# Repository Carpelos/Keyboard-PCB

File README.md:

# Keyboard PCB
 Mi primera PCB de teclado

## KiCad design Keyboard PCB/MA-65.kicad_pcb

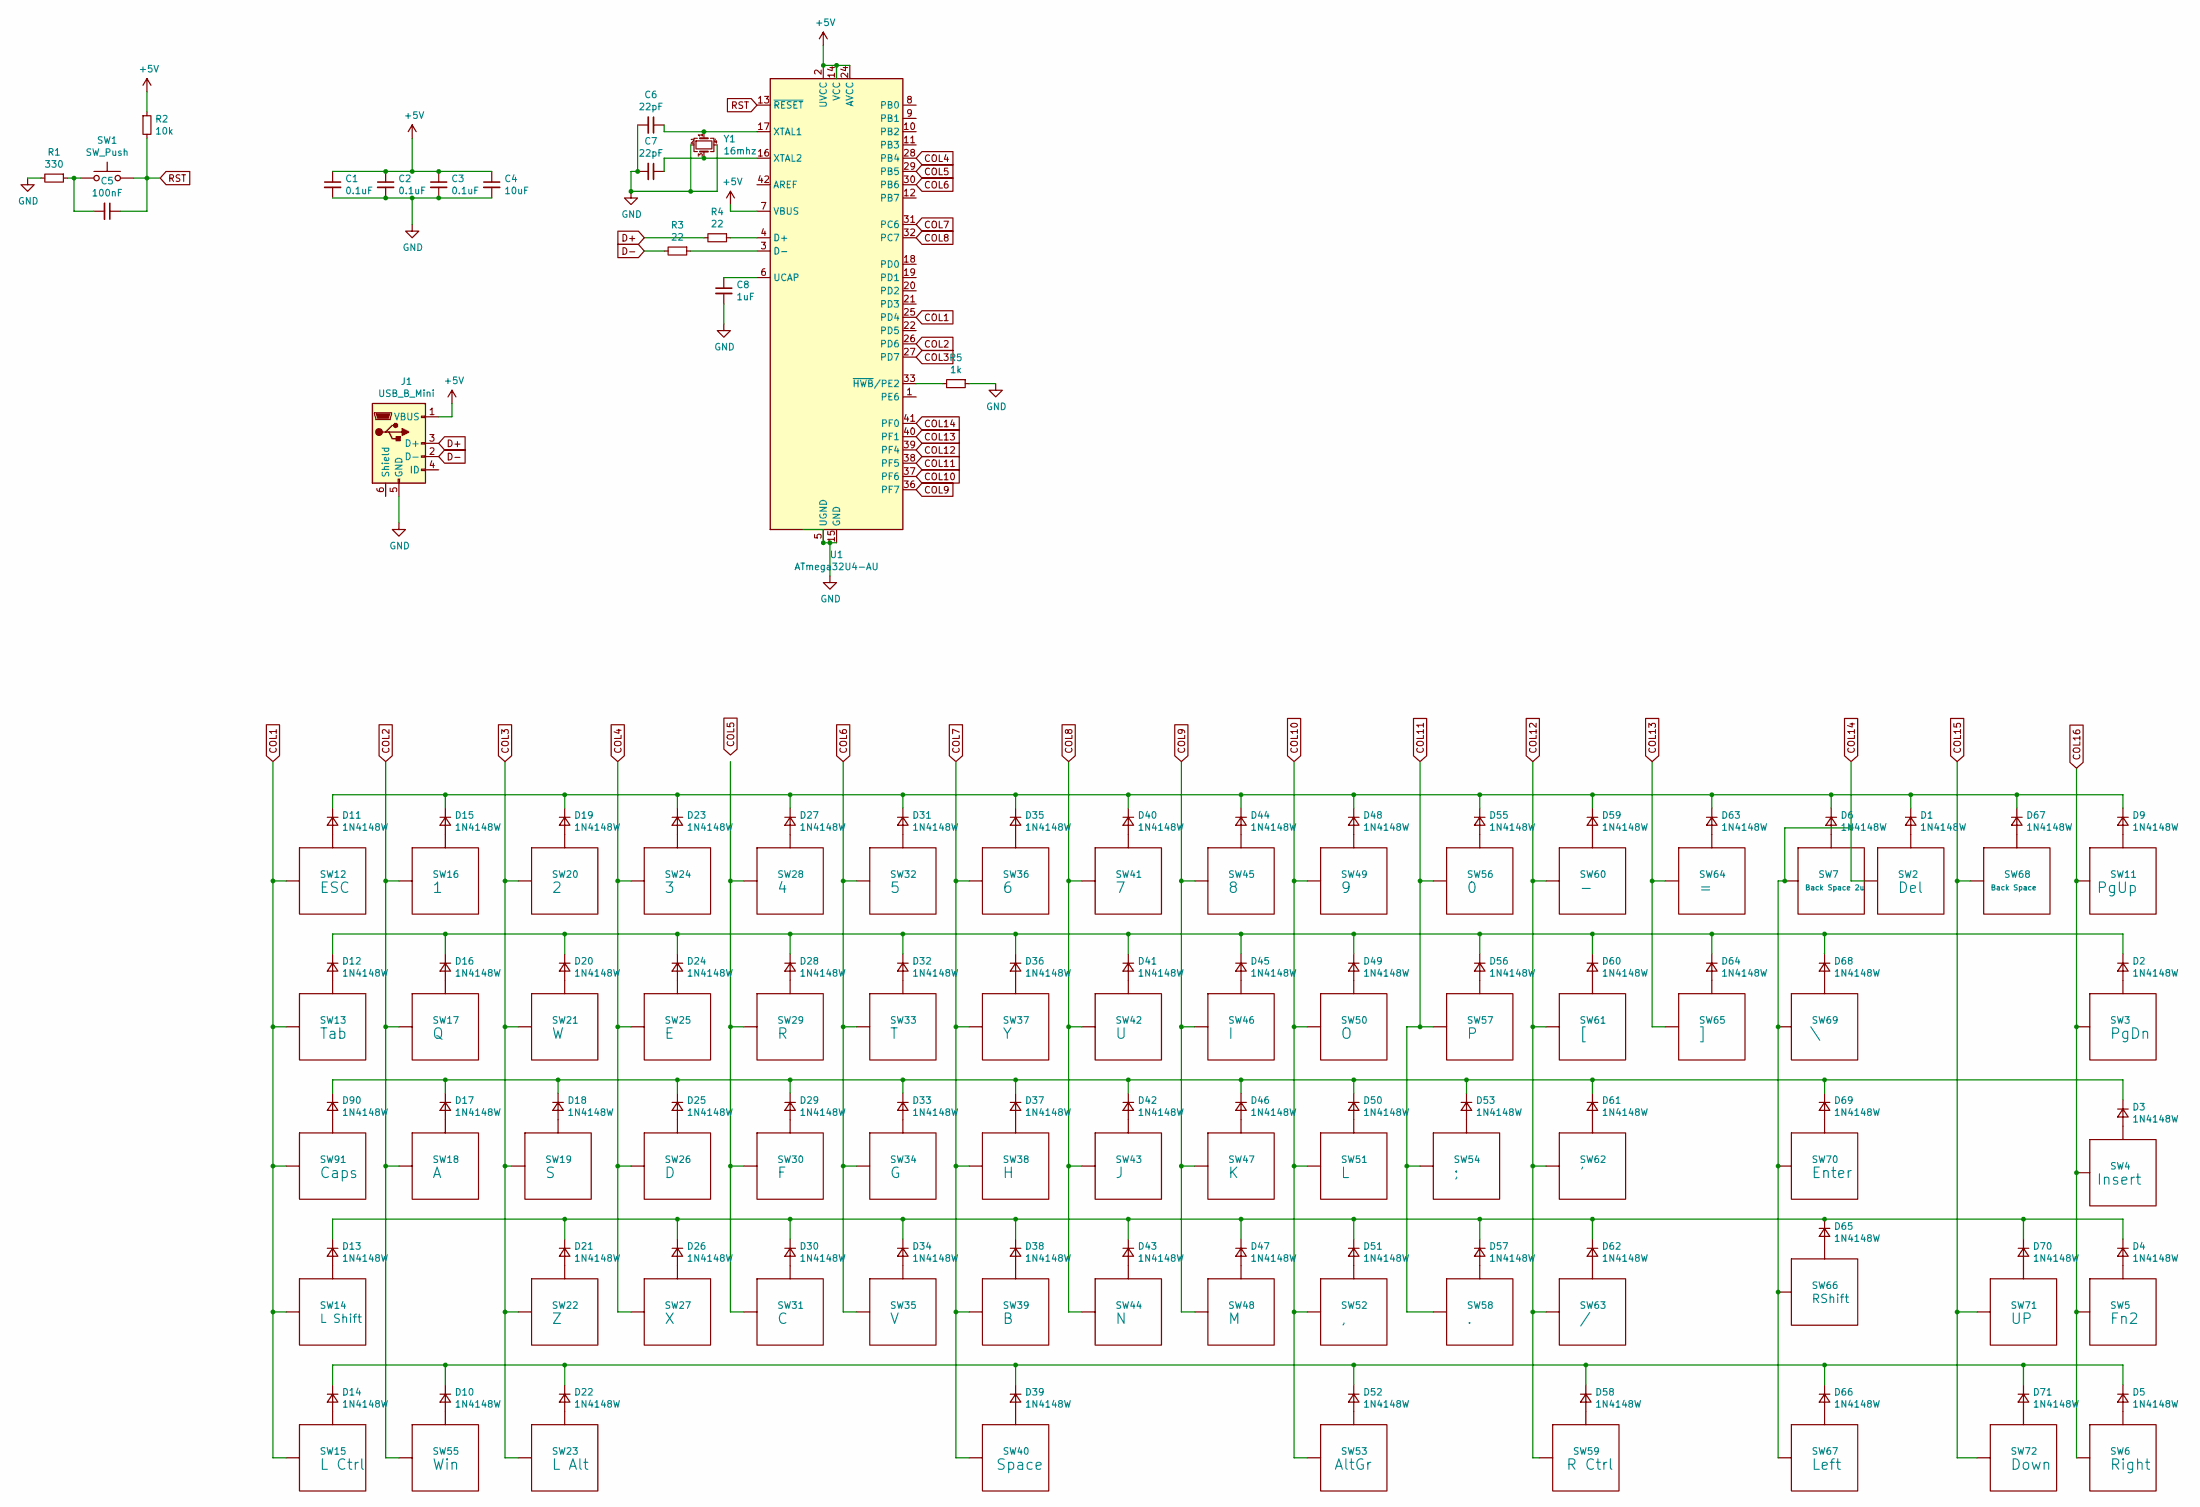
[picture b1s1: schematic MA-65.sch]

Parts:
C1, C2, C3: 0.1uF; D_0805_2012Metric_Pad1.15x1.40mm_HandSolder
C4: 10uF; D_0805_2012Metric_Pad1.15x1.40mm_HandSolder
C5: 100nF; D_0805_2012Metric_Pad1.15x1.40mm_HandSolder
C6, C7: 22pF; D_0805_2012Metric_Pad1.15x1.40mm_HandSolder
C8: 1uF; D_0805_2012Metric_Pad1.15x1.40mm_HandSolder
D1, D2, D3, D4, D5, D6, D9, D10, D11, D12, D13, D14, D15, D16, D17, D18, D19, D20, D21, D22, D23, D24, D25, D26, D27, D28, D29, D30, D31, D32, D33, D34, D35, D36, D37, D38, D39, D40, D41, D42, D43, D44, D45, D46, D47, D48, D49, D50, D51, D52, D53, D55, D56, D57, D58, D59, D60, D61, D62, D63, D64, D65, D66, D67, D68, D69, D70, D71, D90: 1N4148W; D_SOD-123
J1: USB_B_Mini; USB_MiniB_XM7D-0512
R1: 330; R_1206_3216Metric_Pad1.42x1.75mm_HandSolder
R2: 10k; R_1206_3216Metric_Pad1.42x1.75mm_HandSolder
R3, R4: 22; R_1206_3216Metric_Pad1.42x1.75mm_HandSolder
R5: 1k; R_1206_3216Metric_Pad1.42x1.75mm_HandSolder
SW1: SW_Push; smdPushBtn
SW2: Del; MX100
SW3: PgDn; MX100
SW4: Insert; MX100
SW5: Fn2; MX100
SW6: Right; MX100
SW7: Back Space 2u; MX200
SW11: PgUp; MX100
SW12: ESC; MX100
SW13: Tab; MX150
SW14: L Shift; MX225
SW15: L Ctrl; MX125
SW16: 1; MX100
SW17: Q; MX100
SW18: A; MX100
SW19: S; MX100
SW20: 2; MX100
SW21: W; MX100
SW22: Z; MX100
SW23: L Alt; MX125
SW24: 3; MX100
SW25: E; MX100
SW26: D; MX100
SW27: X; MX100
SW28: 4; MX100
SW29: R; MX100
SW30: F; MX100
SW31: C; MX100
SW32: 5; MX100
SW33: T; MX100
SW34: G; MX100
SW35: V; MX100
SW36: 6; MX100
SW37: Y; MX100
SW38: H; MX100
SW39: B; MX100
SW40: Space; MX625
SW41: 7; MX100
SW42: U; MX100
SW43: J; MX100
SW44: N; MX100
SW45: 8; MX100
SW46: I; MX100
SW47: K; MX100
SW48: M; MX100
SW49: 9; MX100
SW50: O; MX100
SW51: L; MX100
SW52: ,; MX100
SW53: AltGr; MX125
SW54: ;; MX100
SW55: Win; MX125
SW56: 0; MX100
SW57: P; MX100
SW58: .; MX100
SW59: R Ctrl; MX125
SW60: -; MX100
SW61: [; MX100
SW62: '; MX100
SW63: /; MX100
SW64: =; MX100
SW65: ]; MX100
SW66: RShift; MX175
SW67: Left; MX100
SW68: Back Space; MX100
SW69: \\; MX150
SW70: Enter; MX225
SW71: UP; MX100
SW72: Down; MX100
SW91: Caps; MX175
U1: ATmega32U4-AU; TQPF-44_10x10mm_P0.8mm
Y1: 16mhz; Crystal_SMD_3225-4Pin_3.2x2.5mm_HandSoldering

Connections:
+5V: C1.1, C2.1, C3.1, C4.1, J1.1 (VBUS), R2.1, U1.2 (UVCC), U1.7 (VBUS), U1.14 (VCC), U1.24 (AVCC), U1.34 (VCC), U1.44 (AVCC)
COL1: SW12.1 (Col), SW13.1 (Col), SW14.1 (Col), SW15.1 (Col), SW91.1 (Col), U1.25 (PD4)
COL2: SW16.1 (Col), SW17.1 (Col), SW18.1 (Col), SW55.1 (Col), U1.26 (PD6)
COL3: SW19.1 (Col), SW20.1 (Col), SW21.1 (Col), SW22.1 (Col), SW23.1 (Col), U1.27 (PD7)
COL4: SW24.1 (Col), SW25.1 (Col), SW26.1 (Col), SW27.1 (Col), U1.28 (PB4)
COL5: U1.29 (PB5)
COL6: SW32.1 (Col), SW33.1 (Col), SW34.1 (Col), SW35.1 (Col), U1.30 (PB6)
COL7: SW36.1 (Col), SW37.1 (Col), SW38.1 (Col), SW39.1 (Col), SW40.1 (Col), U1.31 (PC6)
COL8: SW41.1 (Col), SW42.1 (Col), SW43.1 (Col), SW44.1 (Col), U1.32 (PC7)
COL9: SW45.1 (Col), SW46.1 (Col), SW47.1 (Col), SW48.1 (Col), U1.36 (PF7); also elsewhere on the board
COL10: SW49.1 (Col), SW50.1 (Col), SW51.1 (Col), SW52.1 (Col), SW53.1 (Col), U1.37 (PF6)
COL11: SW54.1 (Col), SW56.1 (Col), SW57.1 (Col), SW58.1 (Col), U1.38 (PF5)
COL12: SW59.1 (Col), SW60.1 (Col), SW61.1 (Col), SW62.1 (Col), SW63.1 (Col), U1.39 (PF4)
COL13: SW64.1 (Col), SW65.1 (Col), U1.40 (PF1)
COL14: SW2.1 (Col), SW7.1 (Col), SW66.1 (Col), SW67.1 (Col), SW69.1 (Col), SW70.1 (Col), U1.41 (PF0)
COL15: SW68.1 (Col), SW71.1 (Col), SW72.1 (Col)
COL16: SW3.1 (Col), SW4.1 (Col), SW5.1 (Col), SW6.1 (Col), SW11.1 (Col)
D+: J1.3 (D+), R4.2
D-: J1.2 (D-), R3.2
GND: C1.2, C2.2, C3.2, C4.2, C6.2, C7.2, C8.2, J1.5 (GND), R1.2, R5.1, U1.5 (UGND), U1.15 (GND), U1.23 (GND), U1.35 (GND), U1.43 (GND), Y1.2, Y1.4
unnamed: C5.2, R1.1, SW1.1
unnamed: C6.1, U1.17 (XTAL1), Y1.1
unnamed: C7.1, U1.16 (XTAL2), Y1.3
unnamed: C8.1, U1.6 (UCAP)
unnamed: D1.1 (K), D6.1 (K), D9.1 (K), D11.1 (K), D15.1 (K), D19.1 (K), D23.1 (K), D27.1 (K), D31.1 (K), D35.1 (K), D40.1 (K), D44.1 (K), D48.1 (K), D55.1 (K), D59.1 (K), D63.1 (K), D67.1 (K)
unnamed: D1.2 (A), SW2.2 (Row)
unnamed: D2.2 (A), SW3.2 (Row)
unnamed: D3.2 (A), SW4.2 (Row)
unnamed: D4.2 (A), SW5.2 (Row)
unnamed: D5.2 (A), SW6.2 (Row)
unnamed: D6.2 (A), SW7.2 (Row)
unnamed: D9.2 (A), SW11.2 (Row)
unnamed: D5.1 (K), D10.1 (K), D14.1 (K), D22.1 (K), D39.1 (K), D52.1 (K), D58.1 (K), D66.1 (K), D71.1 (K)
unnamed: D10.2 (A), SW55.2 (Row)
unnamed: D11.2 (A), SW12.2 (Row)
unnamed: D2.1 (K), D12.1 (K), D16.1 (K), D20.1 (K), D24.1 (K), D28.1 (K), D32.1 (K), D36.1 (K), D41.1 (K), D45.1 (K), D49.1 (K), D56.1 (K), D60.1 (K), D64.1 (K), D68.1 (K)
unnamed: D12.2 (A), SW13.2 (Row)
unnamed: D4.1 (K), D13.1 (K), D21.1 (K), D26.1 (K), D30.1 (K), D34.1 (K), D38.1 (K), D43.1 (K), D47.1 (K), D51.1 (K), D57.1 (K), D62.1 (K), D65.1 (K), D70.1 (K)
unnamed: D13.2 (A), SW14.2 (Row)
unnamed: D14.2 (A), SW15.2 (Row)
unnamed: D15.2 (A), SW16.2 (Row)
unnamed: D16.2 (A), SW17.2 (Row)
unnamed: D3.1 (K), D17.1 (K), D18.1 (K), D25.1 (K), D29.1 (K), D33.1 (K), D37.1 (K), D42.1 (K), D46.1 (K), D50.1 (K), D53.1 (K), D61.1 (K), D69.1 (K), D90.1 (K)
unnamed: D17.2 (A), SW18.2 (Row)
unnamed: D18.2 (A), SW19.2 (Row)
unnamed: D19.2 (A), SW20.2 (Row)
unnamed: D20.2 (A), SW21.2 (Row)
unnamed: D21.2 (A), SW22.2 (Row)
unnamed: D22.2 (A), SW23.2 (Row)
unnamed: D23.2 (A), SW24.2 (Row)
unnamed: D24.2 (A), SW25.2 (Row)
unnamed: D25.2 (A), SW26.2 (Row)
unnamed: D26.2 (A), SW27.2 (Row)
unnamed: D27.2 (A), SW28.2 (Row)
unnamed: D28.2 (A), SW29.2 (Row)
unnamed: D29.2 (A), SW30.2 (Row)
unnamed: D30.2 (A), SW31.2 (Row)
unnamed: D31.2 (A), SW32.2 (Row)
unnamed: D32.2 (A), SW33.2 (Row)
unnamed: D33.2 (A), SW34.2 (Row)
unnamed: D34.2 (A), SW35.2 (Row)
unnamed: D35.2 (A), SW36.2 (Row)
unnamed: D36.2 (A), SW37.2 (Row)
unnamed: D37.2 (A), SW38.2 (Row)
unnamed: D38.2 (A), SW39.2 (Row)
unnamed: D39.2 (A), SW40.2 (Row)
unnamed: D40.2 (A), SW41.2 (Row)
unnamed: D41.2 (A), SW42.2 (Row)
unnamed: D42.2 (A), SW43.2 (Row)
unnamed: D43.2 (A), SW44.2 (Row)
unnamed: D44.2 (A), SW45.2 (Row)
unnamed: D45.2 (A), SW46.2 (Row)
unnamed: D46.2 (A), SW47.2 (Row)
unnamed: D47.2 (A), SW48.2 (Row)
unnamed: D48.2 (A), SW49.2 (Row)
unnamed: D49.2 (A), SW50.2 (Row)
unnamed: D50.2 (A), SW51.2 (Row)
unnamed: D51.2 (A), SW52.2 (Row)
unnamed: D52.2 (A), SW53.2 (Row)
unnamed: D53.2 (A), SW54.2 (Row)
unnamed: D55.2 (A), SW56.2 (Row)
unnamed: D56.2 (A), SW57.2 (Row)
unnamed: D57.2 (A), SW58.2 (Row)
unnamed: D58.2 (A), SW59.2 (Row)
unnamed: D59.2 (A), SW60.2 (Row)
unnamed: D60.2 (A), SW61.2 (Row)
unnamed: D61.2 (A), SW62.2 (Row)
unnamed: D62.2 (A), SW63.2 (Row)
unnamed: D63.2 (A), SW64.2 (Row)
unnamed: D64.2 (A), SW65.2 (Row)
unnamed: D65.2 (A), SW66.2 (Row)
unnamed: D66.2 (A), SW67.2 (Row)
unnamed: D67.2 (A), SW68.2 (Row)
unnamed: D68.2 (A), SW69.2 (Row)
unnamed: D69.2 (A), SW70.2 (Row)
unnamed: D70.2 (A), SW71.2 (Row)
unnamed: D71.2 (A), SW72.2 (Row)
unnamed: D90.2 (A), SW91.2 (Row)
unnamed: R3.1, U1.3 (D-)
unnamed: R4.1, U1.4 (D+)
unnamed: R5.2, U1.33 (~HWB~/PE2)
unnamed: SW28.1 (Col), SW29.1 (Col), SW30.1 (Col), SW31.1 (Col)
RST: C5.1, R2.2, SW1.2, U1.13 (~RESET)

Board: 2 copper layers, 156 parts (0 on the bottom side), 102 nets, no tracks yet.

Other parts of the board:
D8: 1N4148W; D_SOD-123

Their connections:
COL9: D8.1; also elsewhere on the board

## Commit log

2019-09-16 Inicio del proyecto
2019-09-16 Add submodules
2019-09-16 Añadidas las librerías de huellas
2019-09-16 Terminada la zona del MCU
2019-09-16 Metidas las librerías acheron
2019-09-16 Añadida la librería de acheron
2019-09-17 Aplicadas las Huellas
2019-09-17 Nombrando Switches
2019-09-18 ROW2
2019-09-18 row 4
2019-09-18 row 5
2019-09-18 Asignadas huellas
2019-09-19 switches placed
2019-09-19 Diodes placing
2019-09-19 Routing
2019-09-21 Empiezo el diseño de la PCB del MA-65
2019-09-21 Split spacebar Ma-65
2019-09-21 PCB Ma-65
